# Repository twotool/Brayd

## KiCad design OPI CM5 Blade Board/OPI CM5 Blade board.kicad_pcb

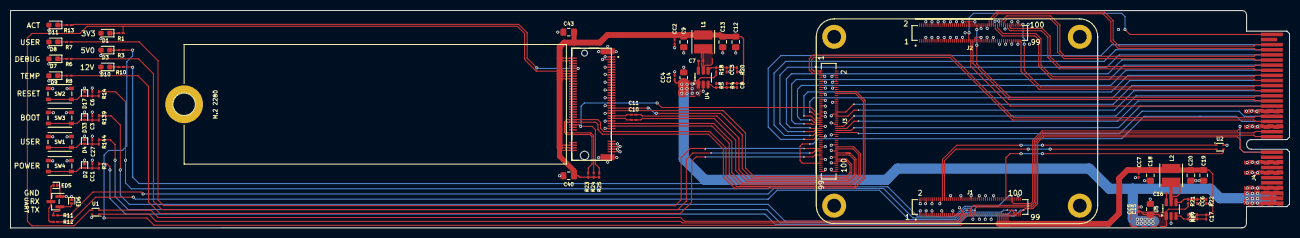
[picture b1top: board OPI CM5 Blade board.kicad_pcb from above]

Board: 4 copper layers, 250.0 x 42.5 mm, 83 parts (0 on the bottom side), 89 nets.

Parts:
C3, C6, C7, C10, C11, C16, C27: 100nF; C_0201_0603Metric_Pad0.64x0.40mm_HandSolder
C8, C17: 22pF; C_0201_0603Metric_Pad0.64x0.40mm_HandSolder
C9, C18, C40, C43: 47μF; C_0805_2012Metric_Pad1.18x1.45mm_HandSolder
C12, C14, C15, C20: 10μF; C_0805_2012Metric_Pad1.18x1.45mm_HandSolder
C13, C19: 22μF; C_0805_2012Metric_Pad1.18x1.45mm_HandSolder
CC1, CC2, CC3, CC4, CC5, CC6, CC7: 100nF; C_0201_0603Metric_Pad0.64x0.40mm_HandSolder
D1, D3: RED; LED_0603_1608Metric_Pad1.05x0.95mm_HandSolder
D2, D4, D17, D33: JEB05DFA; DFN1006-2
D7: ORN; LED_0603_1608Metric_Pad1.05x0.95mm_HandSolder
D8: GRN; LED_0603_1608Metric_Pad1.05x0.95mm_HandSolder
D9, D10: YLO; LED_0603_1608Metric_Pad1.05x0.95mm_HandSolder
D11: BLU; LED_0603_1608Metric_Pad1.05x0.95mm_HandSolder
ED5, ED6: ESD5341N; DFN1006-2
H1, H2, H3, H4: MountingHole_Pad; MountingHole_2.7mm_M2.5_DIN965_Pad
J1: OPi_CM5_CORE JP1 100PIN; HIROSE_DF40C-100DS-0.4V_51_
J2: OPi_CM5_CORE JP2 100PIN; HIROSE_DF40C-100DS-0.4V_51_
J3: OPi_CM5_CORE JP13100PIN; HIROSE_DF40C-100DS-0.4V_51_
J4: Bus_PCI_Express_x4; BUS_PCIexpress_x4
J5: J_1-2199230-5; TE_1-2199230-5
L1, L2: WPN4020H2R2MT
NC/SIP1X3: SIP1X3; PinHeader_1x03_P1.00mm_Vertical_SMD_Pin1Right
R1, R3: 560R; R_0201_0603Metric_Pad0.64x0.40mm_HandSolder
R2, R144: 200R; R_0201_0603Metric_Pad0.64x0.40mm_HandSolder
R4, R18, R20, R21, R22: 100K; R_0201_0603Metric_Pad0.64x0.40mm_HandSolder
R5: 22.1K; R_0201_0603Metric_Pad0.64x0.40mm_HandSolder
R6, R7, R8, R10, R13: 470R; R_0201_0603Metric_Pad0.64x0.40mm_HandSolder
R11, R12: 0R; R_0201_0603Metric_Pad0.64x0.40mm_HandSolder
R14, R139: 100R; R_0201_0603Metric_Pad0.64x0.40mm_HandSolder
R23, R24, R25: 4K7; R_0201_0603Metric_Pad0.64x0.40mm_HandSolder
R26: 110K; R_0201_0603Metric_Pad0.64x0.40mm_HandSolder
R27: 15K; R_0201_0603Metric_Pad0.64x0.40mm_HandSolder
SW1: USER_SW; SW4_PTS815 SJM 250 SMTR LFS_CNK
SW2: RESET_SW; SW4_PTS815 SJM 250 SMTR LFS_CNK
SW3: BOOT_SW; SW4_PTS815 SJM 250 SMTR LFS_CNK
SW4: PWR_SW; SW4_PTS815 SJM 250 SMTR LFS_CNK
U1, U2: SHT40-BD1B-R3; SHT4X
U4, U5: SM8103ADC; SOT-23-6_Handsoldering

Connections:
+3.3V_3A: C8.1, C9.1, C12.1, C13.1, C40.1, C43.1, CC2.1, J5.2 (VCC_3.3), J5.4 (VCC_3.3), J5.12 (VCC_3.3), J5.14 (VCC_3.3), J5.16 (VCC_3.3), J5.18 (VCC_3.3), J5.70 (VCC_3.3), J5.72 (VCC_3.3), J5.74 (VCC_3.3), L1.2, R1.1, R4.2, R23.2, R24.2, R25.2, U1.3 (VDD)
+5V_3A: C17.1, C18.1, C19.1, C20.1, CC7.1, J1.77, J1.79, J1.81, J1.83, J1.85, J1.87, L2.2, R3.1, R26.2
+12V: C14.1, C15.1, CC4.1, CC5.1, J4.A1, J4.A2, J4.A3, J4.B1, J4.B2, J4.B3, R10.1, R18.1, R21.1, U4.1 (BS), U5.1 (BS)
/+1.8V: J4.A10, J4.B10
/+3.3V: J4.A8, J4.B8
/+5V: J4.A5, J4.A6, J4.B5, J4.B6
/BOOT_KEY: J1.93, R139.1
/DEBUG_LED: J3.79, R6.1
/GMAC_MCLK: J3.57, J4.A27
/GMAC_MDC: J3.91, J4.A15
/GMAC_MDIO: J3.53, J4.A26
/GMAC_RXCLK: J3.58, J4.A19
/GMAC_RXD0: J3.60, J4.A18
/GMAC_RXD1: J3.56, J4.A20
/GMAC_RXD2: J3.61, J4.A29
/GMAC_RXD3: J3.63, J4.A30
/GMAC_RXDV: J3.59, J4.A28
/GMAC_TXCLK: J3.62, J4.A16
/GMAC_TXD0: J3.46, J4.A21
/GMAC_TXD1: J3.49, J4.A24
/GMAC_TXD2: J3.47, J4.A23
/GMAC_TXD3: J3.42, J4.A22
/GMAC_TXEN: J3.51, J4.A25
/HDMI0_SBDN: J2.53, J4.B19
/HDMI0_SBDP: J2.58, J4.B20
/HDMI0_TX0N: J2.84, J4.B27
/HDMI0_TX0P: J2.82, J4.B28
/HDMI0_TX1N: J2.78, J4.B24
/HDMI0_TX1P: J2.76, J4.B23
/HDMI0_TX2N: J2.72, J4.B29
/HDMI0_TX2P: J2.70, J4.B30
/HDMI0_TX3N: J2.90, J4.B26
/HDMI0_TX3P: J2.88, J4.B25
/HDMI0_TX_CEC_M0: J2.51, J4.B18
/HDMI0_TX_ON_H: J2.49, J4.B32
/HDMI0_TX_SCL_M0: J2.100, J4.B22
/HDMI0_TX_SDA_M0: J2.99, J4.B21
/I2C3_SCL_M0: J1.26, U2.2 (SCL)
/I2C3_SDA_M0: J1.24, U2.1 (SDA)
/I2C5_SCL_M3: J1.41, U1.2 (SCL)
/I2C5_SDA_M3: J1.45, U1.1 (SDA)
/M.2_ACT: J5.10 (DAS/DSS), R13.1
/MIPI_CSI0_D2N: J2.33, J2.35
/PCIE20_0_REFCLKN: J3.78, J5.53 (REFCLKN)
/PCIE20_0_REFCLKP: J3.76, J5.55 (REFCLKP)
/PCIE20_0_RXN: J3.88, J5.41 (SATA_B+/PERN0)
/PCIE20_0_RXP: J3.90, J5.43 (SATA_B-/PERP0)
/PCIE20_0_TXN: C11.2, J3.84
/PCIE20_0_TXP: C10.2, J3.82
/PCIE20x1_2_CLKREQn_M0: J3.22, J5.52 (~CLKREQ), R24.1
/PCIE20x1_2_PERSTn_M0: J3.24, J5.50 (~PERST), R23.1
/PCIE20x1_2_WAKEn_M0: J3.43, J5.54 (~PEWAKE), R25.1
/PMIC_RESET_L: J1.92, J4.A11, R14.1
/PWRON_L: J1.99, J4.B11, R2.1
/Reserved: J1.3, J1.4, J1.5, J1.6, J1.9, J1.10, J1.11, J1.12, J1.15, J1.16, J1.17, J1.18, J1.19, J1.20, J1.64, J1.70, J1.72, J1.73, J1.89, J1.91, J2.11, J2.46, J2.48, J2.52, J2.54, J2.60, J2.64, J2.66
/TMP_SN1_LED: J3.83, R8.1
/TYPEC0_SSRX1P: J3.19, J3.21
/UART2_RX: J1.51, J4.B13, R12.1
/UART2_TX: J1.55, J4.B12, R11.1
/USB20_HOST1_DN: J3.1, J4.B15
/USB20_HOST1_DP: J3.3, J4.B16
/USER_KEY: J1.95, R144.1
/USER_LED: J3.77, R7.1
/VCC_1V8_S3: J1.88, J1.90
/VCC_3V3_S3: J1.78, J1.84, J1.86, U2.3 (VDD)
GND: C3.2, C6.2, C9.2, C12.2, C13.2, C14.2, C15.2, C18.2, C19.2, C20.2, C27.2, C40.2, C43.2, CC1.2, CC2.2, CC3.2, CC4.2, CC5.2, CC6.2, CC7.2, D1.2 (A), D2.1 (A1), D3.2 (A), D4.1 (A1), D7.2 (A), D8.2 (A), D9.2 (A), D10.2 (A), D11.2 (A), D17.1 (A1), D33.1 (A1), ED5.1 (A1), ED6.1 (A1), J1.1, J1.2, J1.7, J1.8, J1.13, J1.14, J1.22, J1.23, J1.32, J1.33, J1.42, J1.43, J1.52, J1.53, J1.59, J1.60, J1.65, J1.66, J1.71, J1.74, J1.98, J2.7, J2.8, J2.13, J2.14, J2.19, J2.20, J2.25, J2.26, J2.31, J2.32, J2.37, J2.38, J2.43, J2.44, J2.50, J2.55, J2.56, J2.61, J2.62, J2.67, J2.68, J2.73, J2.74, J2.79, J2.80, J2.85, J2.86, J2.91, J2.92, J2.97, J2.98, J3.5, J3.6, J3.11, J3.12, J3.17, J3.18, J3.23, J3.29, J3.32, J3.35, J3.41, J3.44, J3.45, J3.54, J3.55, J3.64, J3.65, J3.74, J3.75, J3.80, J3.86, J3.87, J3.92, J3.99, J3.100, J4.A4, J4.A7, J4.A9, J4.A14, J4.A17, J4.B4, J4.B7, J4.B9, J4.B14, J4.B17, J5.1 (CONFIG_3), J5.3 (GND), J5.9 (GND), J5.15 (GND), J5.21 (CONFIG_0), J5.27 (GND), J5.33 (GND), J5.39 (GND), J5.45 (GND), J5.51 (GND), J5.57 (GND), J5.69 (CONFIG_1), J5.71 (GND), J5.73 (GND), J5.75 (CONFIG_2), J5.80 (GND), J5.S1 (GND), J5.S2 (GND), NC/SIP1X3.1, R5.1, R20.2, R22.2, R27.1, SW1.1, SW1.2, SW2.1, SW2.2, SW3.1, SW3.2, SW4.1, SW4.2, U1.4 (VSS), U2.4 (VSS), U4.2 (GND), U5.2 (GND)
unnamed: D1.1 (K), R1.2
unnamed: CC1.1, D2.2 (A2), R2.2, SW4.3, SW4.4
unnamed: D3.1 (K), R3.2
unnamed: C27.1, D4.2 (A2), R144.2, SW1.3, SW1.4
unnamed: D7.1 (K), R6.2
unnamed: D8.1 (K), R7.2
unnamed: D9.1 (K), R8.2
unnamed: D10.1 (K), R10.2
unnamed: D11.1 (K), R13.2
unnamed: C6.1, D17.2 (A2), R14.2, SW2.3, SW2.4
unnamed: C3.1, D33.2 (A2), R139.2, SW3.3, SW3.4
unnamed: ED5.2 (A2), NC/SIP1X3.2, R12.2
unnamed: ED6.2 (A2), NC/SIP1X3.3, R11.2
unnamed: C10.1, J5.49 (SATA_A+/PETP0)
unnamed: C11.1, J5.47 (SATA_A-/PETN0)
unnamed: CC3.1, R18.2, R20.1, U4.4 (EN)
unnamed: C8.2, R4.1, R5.2, U4.3 (FB)
unnamed: C7.1, U4.6 (LX)
unnamed: C7.2, L1.1, U4.5 (VIN)
unnamed: CC6.1, R21.2, R22.1, U5.4 (EN)
unnamed: C17.2, R26.1, R27.2, U5.3 (FB)
unnamed: C16.1, U5.6 (LX)
unnamed: C16.2, L2.1, U5.5 (VIN)

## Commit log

2025-05-09 Firt commit
2025-05-09 LED SW added in schematic
2025-05-09 Docs added
2025-05-12 Working on HDMI PCIe connector wiring
2025-05-13 Working on USB differential pairs
2025-05-13 Wroking on USB differential pair
2025-05-14 Working on M.2 SSD
2025-05-15 M.2 SSD schematic complete
2025-05-20 New M.2 Symbol complete
2025-05-26 Working on routing
2025-06-01 Project complete
2025-06-02 gerber files geneated

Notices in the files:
parts and their libraries:
Copyright 2016 Accelerated Designs. All rights reserved.
